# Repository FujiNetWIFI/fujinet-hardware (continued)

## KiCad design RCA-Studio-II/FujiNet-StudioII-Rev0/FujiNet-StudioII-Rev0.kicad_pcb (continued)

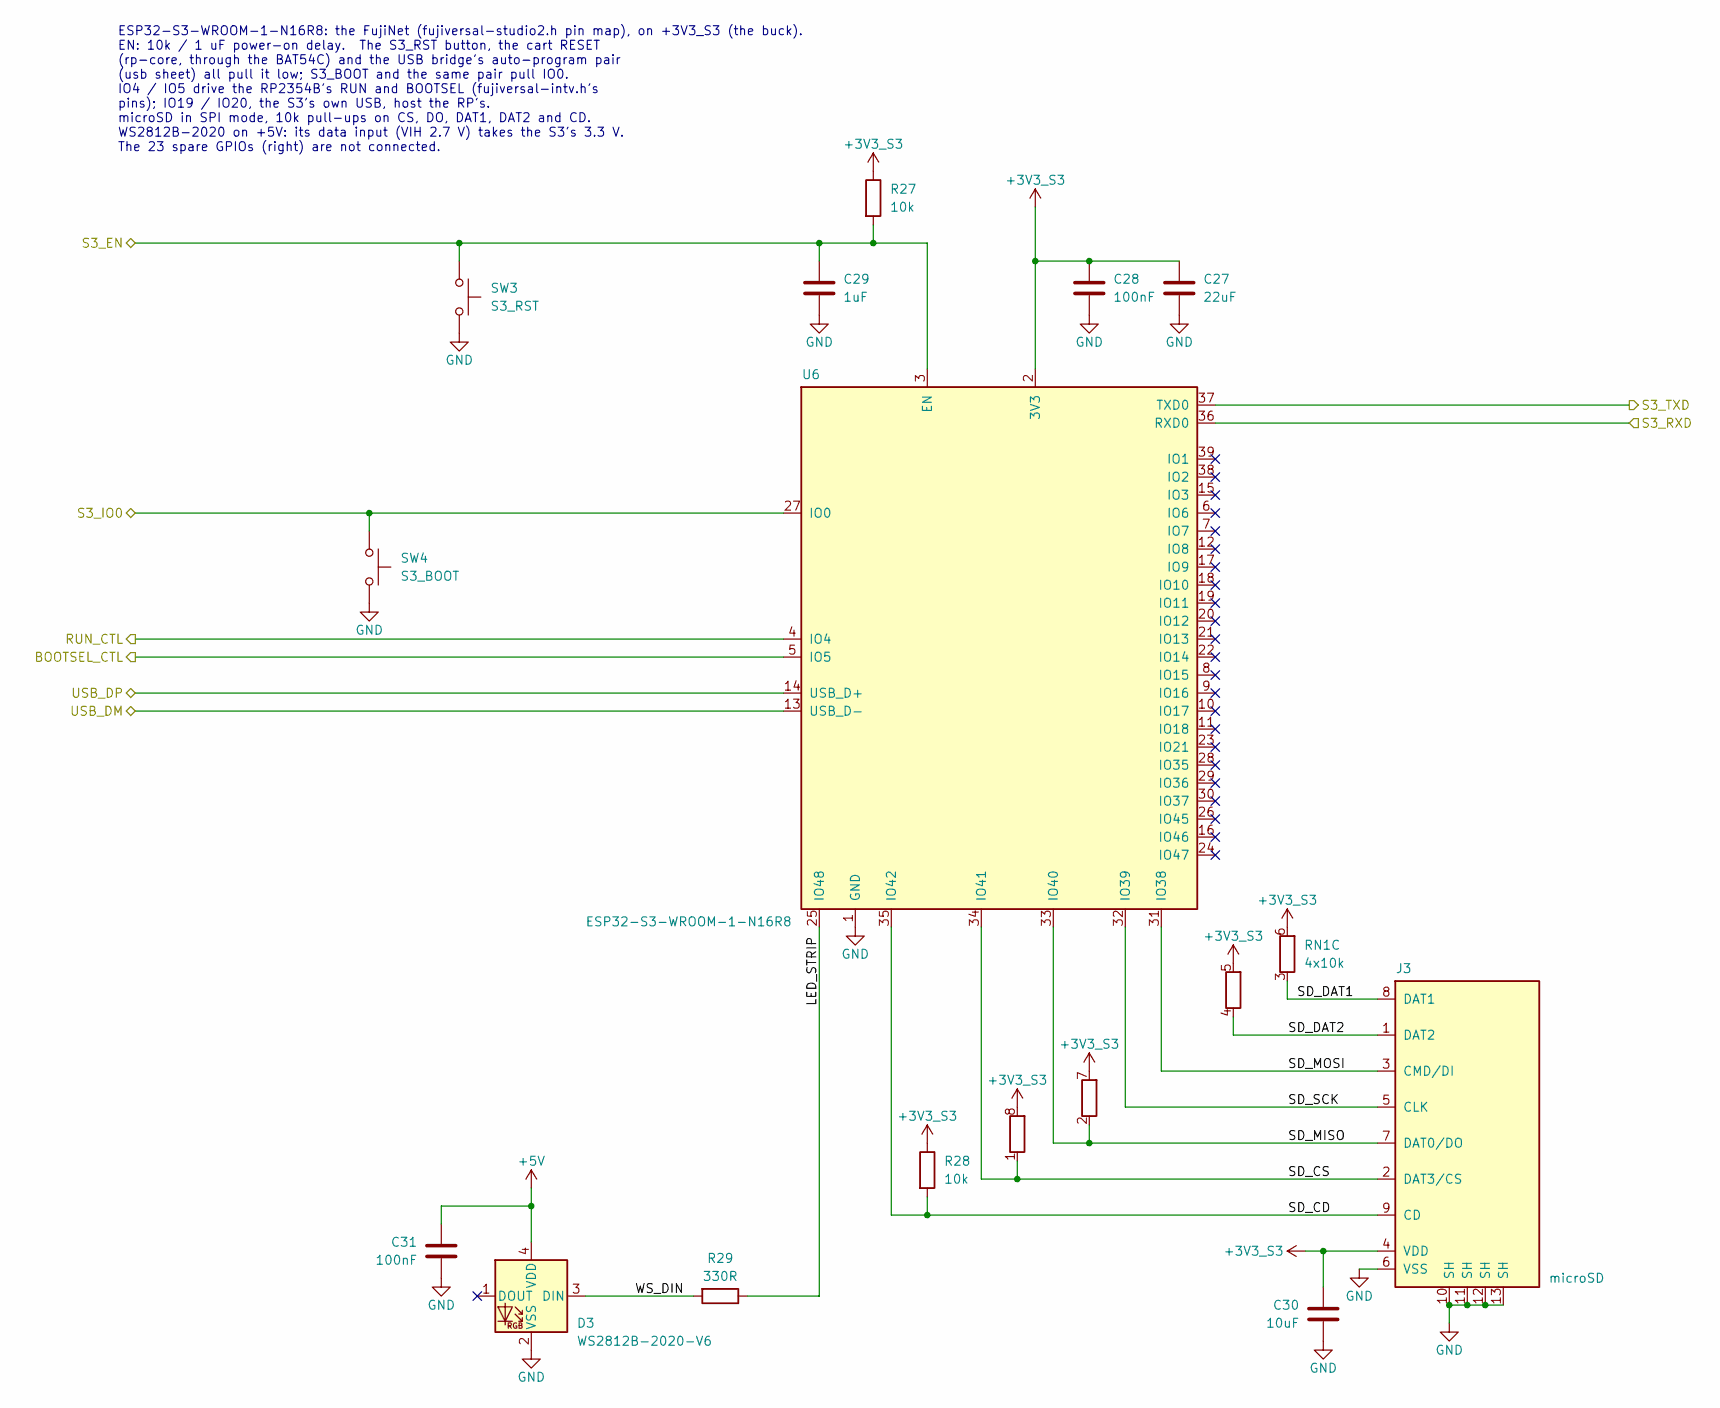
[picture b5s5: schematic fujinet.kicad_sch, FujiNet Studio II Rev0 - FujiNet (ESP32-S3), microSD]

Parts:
C27: 22uF; C_0805_2012Metric; MPN CL21A226MAQNNNE; LCSC C45783
C28, C31: 100nF; C_0603_1608Metric; MPN CC0603KRX7R9BB104; LCSC C14663
C29: 1uF; C_0603_1608Metric; MPN CL10A105KB8NNNC; LCSC C15849
C30: 10uF; C_0603_1608Metric; MPN CL10A106KP8NNNC; LCSC C19702
D3: WS2812B-2020-V6; LED_WS2812B-2020_PLCC4_2.0x2.0mm; MPN WS2812B-2020-V6; LCSC C52917434
J3: microSD; TF-SMD_TF-015; MPN TF-015; LCSC C113206
R27, R28: 10k; R_0603_1608Metric; MPN 0603WAF1002T5E; LCSC C25804
R29: 330R; R_0603_1608Metric; MPN 0603WAF3300T5E; LCSC C23138
RN1: 4x10k; R_Array_Convex_4x0603; MPN 4D03WGJ0103T5E; LCSC C29718
SW3: S3_RST; SW_SPST_TS-1187A; MPN TS-1187A-B-A-B; LCSC C318884
SW4: S3_BOOT; SW_SPST_TS-1187A; MPN TS-1187A-B-A-B; LCSC C318884
U6: ESP32-S3-WROOM-1-N16R8; ESP32-S3-WROOM-1; MPN ESP32-S3-WROOM-1-N16R8; LCSC C2913202

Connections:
+3V3_S3: C27.1, C28.1, C30.1, J3.4 (VDD), R27.1, R28.1, RN1.5 (R4.2), RN1.6 (R3.2), RN1.7 (R2.2), RN1.8 (R1.2), U6.2 (3V3); also elsewhere on the board
+5V: C31.1, D3.4 (VDD); also elsewhere on the board
/BOOTSEL_CTL: U6.5 (IO5); also elsewhere on the board
/RUN_CTL: U6.4 (IO4); also elsewhere on the board
/S3_EN: C29.1, R27.2, SW3.1, U6.3 (EN); also elsewhere on the board
/S3_IO0: SW4.1, U6.27 (IO0); also elsewhere on the board
/S3_RXD: U6.36 (RXD0); also elsewhere on the board
/S3_TXD: U6.37 (TXD0); also elsewhere on the board
/USB_DM: U6.13 (USB_D-); also elsewhere on the board
/USB_DP: U6.14 (USB_D+); also elsewhere on the board
/fujinet/LED_STRIP: R29.1, U6.25 (IO48)
/fujinet/SD_CD: J3.9 (CD), R28.2, U6.35 (IO42)
/fujinet/SD_CS: J3.2 (DAT3/CS), RN1.1 (R1.1), U6.34 (IO41)
/fujinet/SD_DAT1: J3.8 (DAT1), RN1.3 (R3.1)
/fujinet/SD_DAT2: J3.1 (DAT2), RN1.4 (R4.1)
/fujinet/SD_MISO: J3.7 (DAT0/DO), RN1.2 (R2.1), U6.33 (IO40)
/fujinet/SD_MOSI: J3.3 (CMD/DI), U6.31 (IO38)
/fujinet/SD_SCK: J3.5 (CLK), U6.32 (IO39)
/fujinet/WS_DIN: D3.3 (DIN), R29.2
GND: C27.2, C28.2, C29.2, C30.2, C31.2, D3.2 (VSS), J3.6 (VSS), J3.10 (SH), J3.11 (SH), J3.12 (SH), J3.13 (SH), SW3.2, SW4.2, U6.1 (GND), U6.40 (GND), U6.41 (GND); also elsewhere on the board

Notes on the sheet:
ESP32-S3-WROOM-1-N16R8: the FujiNet (fujiversal-studio2.h pin map), on +3V3_S3 (the buck). EN: 10k / 1 uF power-on delay. The S3_RST button, the cart RESET (rp-core, through the BAT54C) and the USB bridge's auto-program pair (usb sheet) all pull it low; S3_BOOT and the same pair pull IO0. IO4 / IO5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

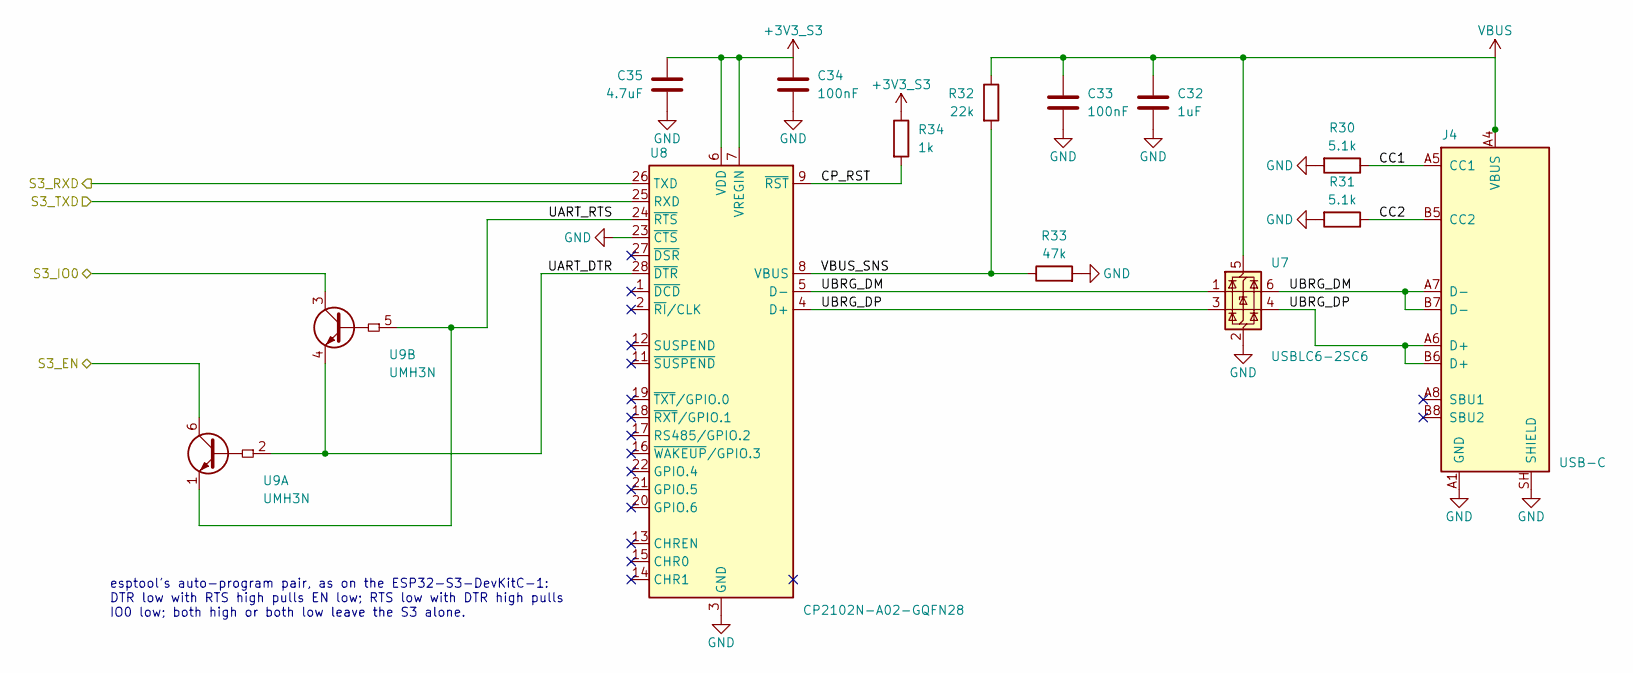
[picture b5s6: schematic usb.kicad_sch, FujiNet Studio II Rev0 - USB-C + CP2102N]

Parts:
C32: 1uF; C_0603_1608Metric; MPN CL10A105KB8NNNC; LCSC C15849
C33, C34: 100nF; C_0603_1608Metric; MPN CC0603KRX7R9BB104; LCSC C14663
C35: 4.7uF; C_0603_1608Metric; MPN CL10A475KO8NNNC; LCSC C19666
J4: USB-C; USB_C_Receptacle_HRO_TYPE-C-31-M-12; MPN TYPE-C-31-M-12; LCSC C165948
R30, R31: 5.1k; R_0603_1608Metric; MPN 0603WAF5101T5E; LCSC C23186
R32: 22k; R_0603_1608Metric; MPN 0603WAF2202T5E; LCSC C31850
R33: 47k; R_0603_1608Metric; MPN 0603WAF4702T5E; LCSC C25819
R34: 1k; R_0603_1608Metric; MPN 0603WAF1001T5E; LCSC C21190
U7: USBLC6-2SC6; SOT-23-6; MPN USBLC6-2SC6; LCSC C7519
U8: CP2102N-A02-GQFN28; QFN-28-1EP_5x5mm_P0.5mm_EP3.35x3.35mm; MPN CP2102N-A02-GQFN28R; LCSC C964632
U9: UMH3N; SOT-363_SC-70-6; MPN UMH3N; LCSC C62892

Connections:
+3V3_S3: C34.1, C35.1, R34.1, U8.6 (VDD), U8.7 (VREGIN); also elsewhere on the board
/S3_EN: U9.6 (C1); also elsewhere on the board
/S3_IO0: U9.3 (C2); also elsewhere on the board
/S3_RXD: U8.26 (TXD); also elsewhere on the board
/S3_TXD: U8.25 (RXD); also elsewhere on the board
/usb/CC1: J4.A5 (CC1), R30.1
/usb/CC2: J4.B5 (CC2), R31.1
/usb/CP_RST: R34.2, U8.9 (~RST)
/usb/UART_DTR: U8.28 (~DTR), U9.2 (B1), U9.4 (E2)
/usb/UART_RTS: U8.24 (~RTS), U9.1 (E1), U9.5 (B2)
/usb/UBRG_DM: J4.A7 (D-), J4.B7 (D-), U7.1 (I/O1), U7.6 (I/O1), U8.5 (D-)
/usb/UBRG_DP: J4.A6 (D+), J4.B6 (D+), U7.3 (I/O2), U7.4 (I/O2), U8.4 (D+)
/usb/VBUS_SNS: R32.2, R33.1, U8.8 (VBUS)
GND: C32.2, C33.2, C34.2, C35.2, J4.A1 (GND), J4.A12 (GND), J4.B1 (GND), J4.B12 (GND), J4.SH (SHIELD), R30.2, R31.2, R33.2, U7.2 (GND), U8.3 (GND), U8.23 (~CTS), U8.29 (GND); also elsewhere on the board
VBUS: C32.1, C33.1, J4.A4 (VBUS), J4.A9 (VBUS), J4.B4 (VBUS), J4.B9 (VBUS), R32.1, U7.5 (VBUS); also elsewhere on the board

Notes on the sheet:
esptool's auto-program pair, as on the ESP32-S3-DevKitC-1: DTR low with RTS high pulls EN low; RTS low with DTR high pulls IO0 low; both high or both low leave the S3 alone.

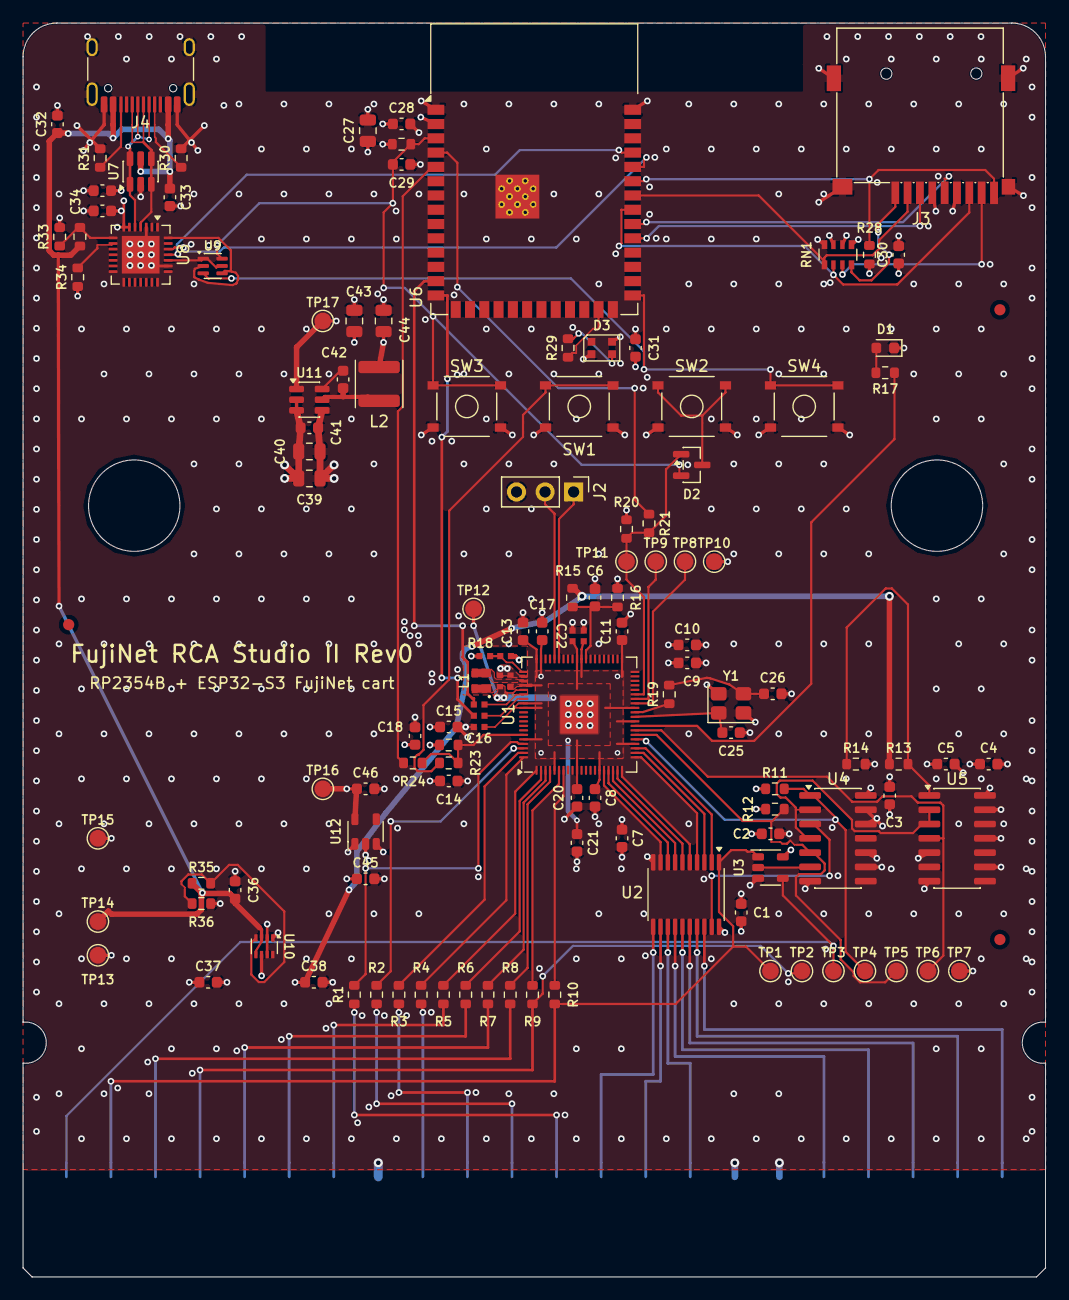
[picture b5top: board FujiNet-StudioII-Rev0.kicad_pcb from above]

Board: 4 copper layers, 90.9 x 111.5 mm, 131 parts (0 on the bottom side), 97 nets.

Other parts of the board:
FID1, FID2, FID3: Fiducial_1mm_Mask2mm
H1, H2: MountingHole_8.128mm_NPTH

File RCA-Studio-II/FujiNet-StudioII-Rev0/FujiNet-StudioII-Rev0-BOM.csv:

Qty,References,Value,Footprint,MPN,Manufacturer,LCSC,Description,Notes
23,C1 C2 C3 C4 C6 C7 C8 C9 C10 C11 C13 C14 C15 C17 C20 C21 C28 C31 C33 C34 C38 C41 C42,100nF,C_0603_1608Metric,CC0603KRX7R9BB104,YAGEO,C14663,capacitor (several uses: see schematic),
4,C5 C18 C30 C37,10uF,C_0603_1608Metric,CL10A106KP8NNNC,Samsung Electro-Mechanics,C19702,capacitor (several uses: see schematic),
3,C12 C16 C22,100nF,RPI_C0402,CL05B104KO5NNNC,Samsung Electro-Mechanics,C1525,capacitor (several uses: see schematic),
2,C19 C23,4.7uF,RPI_C0402_wide,CL05A475MP5NRNC,Samsung Electro-Mechanics,C23733,capacitor (several uses: see schematic),
1,C24,4.7uF,RPI_C0402,CL05A475MP5NRNC,Samsung Electro-Mechanics,C23733,VREG_AVDD filter,
2,C25 C26,15pF,C_0603_1608Metric,CL10C150JB8NNNC,Samsung Electro-Mechanics,C1644,crystal load,
5,C27 C39 C40 C43 C44,22uF,C_0805_2012Metric,CL21A226MAQNNNE,Samsung Electro-Mechanics,C45783,capacitor (several uses: see schematic),
5,C29 C32 C36 C45 C46,1uF,C_0603_1608Metric,CL10A105KB8NNNC,Samsung Electro-Mechanics,C15849,capacitor (several uses: see schematic),
1,C35,4.7uF,C_0603_1608Metric,CL10A475KO8NNNC,Samsung Electro-Mechanics,C19666,CP2102N VDD bulk,
1,D1,red,LED_0603_1608Metric,KT-0603R,Hubei KENTO Elec,C2286,activity LED (GPIO27),
1,D2,BAT54C,SOT-23,"BAT54C,215",Nexperia,C37704,"RESET steering, common cathode",
1,D3,WS2812B-2020-V6,LED_WS2812B-2020_PLCC4_2.0x2.0mm,WS2812B-2020-V6,Worldsemi,C52917434,status LED on +5V (datasheet VDD 3.7-5.3 V; VIH 2.7 V takes 3.3 V data),
1,J1,StudioII_Cart_Edge_22,StudioII_Cart_Edge_22,,,,"RCA Studio II 22-pin cartridge edge, 0.156"" (3.9624 mm) pitch, contacts on one face (B.Cu), FliP multicart geometry",not in BOM
1,J2,DBG UART,PinHeader_1x03_P2.54mm_Vertical,PZ254V-11-03P,XFCN,C2937625,"RP debug UART, 3.3 V: 1 TX (GPIO44), 2 RX (GPIO45), 3 GND; fit for bring-up",DNP
1,J3,microSD,TF-SMD_TF-015,TF-015,SOFNG,C113206,"microSD push-push, SPI mode",
1,J4,USB-C,USB_C_Receptacle_HRO_TYPE-C-31-M-12,TYPE-C-31-M-12,Korean Hroparts Elec,C165948,power + S3 programming / console,
1,L1,3.3uH,RPI_L_AOTA-B201610S3R3,AOTA-B201610S3R3-101-T,Abracon,C42411119,RP2350 core SMPS inductor,
1,L2,6.8uH,L_Sunlord_SWPA4030S,SWPA4030S6R8MT,Sunlord,C62684,buck inductor,
11,R1 R2 R3 R4 R5 R6 R7 R8 R9 R10 R29,330R,R_0603_1608Metric,0603WAF3300T5E,UNI-ROYAL,C23138,resistor (several uses: see schematic),
7,R11 R12 R20 R22 R27 R28 R36,10k,R_0603_1608Metric,0603WAF1002T5E,UNI-ROYAL,C25804,resistor (several uses: see schematic),
2,R13 R32,22k,R_0603_1608Metric,0603WAF2202T5E,UNI-ROYAL,C31850,resistor (several uses: see schematic),
3,R14 R15 R16,100k,R_0603_1608Metric,0603WAF1003T5E,UNI-ROYAL,C25803,resistor (several uses: see schematic),
6,R17 R19 R21 R23 R24 R34,1k,R_0603_1608Metric,0603WAF1001T5E,UNI-ROYAL,C21190,resistor (several uses: see schematic),
1,R18,33R,RPI_R0402,0402WGF330JTCE,UNI-ROYAL,C25105,VREG_AVDD filter,
2,R25 R26,27R,RPI_R0402,0402WGF270JTCE,UNI-ROYAL,C25100,USB series,
2,R30 R31,5.1k,R_0603_1608Metric,0603WAF5101T5E,UNI-ROYAL,C23186,UFP Rd,
1,R33,47k,R_0603_1608Metric,0603WAF4702T5E,UNI-ROYAL,C25819,VBUS sense divider,
1,R35,33k,R_0603_1608Metric,0603WAF3302T5E,UNI-ROYAL,C4216,mux priority threshold (VBUS > 4.3 V),
1,RN1,4x10k,R_Array_Convex_4x0603,4D03WGJ0103T5E,UNI-ROYAL,C29718,SD pull-ups,
1,SW1,BOOTSEL,SW_SPST_TS-1187A,TS-1187A-B-A-B,XKB Connection,C318884,RP2354 BOOTSEL (hold while pressing RESET),
1,SW2,RESET,SW_SPST_TS-1187A,TS-1187A-B-A-B,XKB Connection,C318884,cart RESET: RP RUN + S3 EN via BAT54C,
1,SW3,S3_RST,SW_SPST_TS-1187A,TS-1187A-B-A-B,XKB Connection,C318884,ESP32-S3 EN,
1,SW4,S3_BOOT,SW_SPST_TS-1187A,TS-1187A-B-A-B,XKB Connection,C318884,ESP32-S3 BOOT (IO0),
1,TP1,/MRD,TestPoint_Pad_D1.5mm,,,,scope pad: console /MRD (edge 21),not in BOM
1,TP2,TPA,TestPoint_Pad_D1.5mm,,,,"scope pad: console TPA, gated by /MRD (edge 19)",not in BOM
1,TP3,CART_CS,TestPoint_Pad_D1.5mm,,,,scope pad: CART CS (edge 22),not in BOM
1,TP4,/DRIVE,TestPoint_Pad_D1.5mm,,,,scope pad: /DRIVE (GPIO24),not in BOM
1,TP5,/CLAIM,TestPoint_Pad_D1.5mm,,,,scope pad: NOR input (GPIO25),not in BOM
1,TP6,PWR_OK,TestPoint_Pad_D1.5mm,,,,scope pad: console power sense,not in BOM
2,TP7 TP10,GND,TestPoint_Pad_D1.5mm,,,,test pad (several uses: see schematic),not in BOM
1,TP8,SWCLK,TestPoint_Pad_D1.5mm,,,,test pad,not in BOM
1,TP9,SWDIO,TestPoint_Pad_D1.5mm,,,,test pad,not in BOM
1,TP11,RUN,TestPoint_Pad_D1.5mm,,,,test pad,not in BOM
1,TP12,DVDD,TestPoint_Pad_D1.5mm,,,,bring-up pad: RP core rail,not in BOM
1,TP13,CONS_5V,TestPoint_Pad_D1.5mm,,,,bring-up pad: console 5V (edge 15),not in BOM
1,TP14,VBUS,TestPoint_Pad_D1.5mm,,,,bring-up pad: USB VBUS,not in BOM
1,TP15,+5V,TestPoint_Pad_D1.5mm,,,,bring-up pad: +5V,not in BOM
1,TP16,+3V3,TestPoint_Pad_D1.5mm,,,,bring-up pad: +3V3 (RP),not in BOM
1,TP17,+3V3_S3,TestPoint_Pad_D1.5mm,,,,bring-up pad: +3V3_S3 (S3 side),not in BOM
1,U1,RP2354B,QFN-80-1EP_10x10mm_P0.4mm_EP3.4x3.4mm,RP2354B,Raspberry Pi,C39843328,RP2350B + 2MB flash in package; cart bus server,
1,U2,74HCT541,TSSOP-20_4.4x6.5mm_P0.65mm,SN74HCT541PWR,Texas Instruments,C436096,D0-D7 driver: drives only while /OE1 (/MRD) and /OE2 (/DRIVE) are low,
1,U3,74HCT1G02,SOT-23-5,"74HCT1G02GV,125",Nexperia,C12504,"CART CS = NOR(/MRD, CS_REQ_N), 5 V CMOS out",
1,U4,74HCT32,SOIC-14_3.9x8.7mm_P1.27mm,SN74HCT32DR,Texas Instruments,C6781,/OE2 = /DRIVE | /PWROK; CS_REQ_N = /CLAIM | /PWROK,
1,U5,74HCT14,SOIC-14_3.9x8.7mm_P1.27mm,SN74HCT14DR,Texas Instruments,C6769,PWR_OK from the console 5V sense,
1,U6,ESP32-S3-WROOM-1-N16R8,ESP32-S3-WROOM-1,ESP32-S3-WROOM-1-N16R8,Espressif,C2913202,FujiNet core (fujiversal-studio2),
1,U7,USBLC6-2SC6,SOT-23-6,USBLC6-2SC6,STMicroelectronics,C7519,"USB ESD: D+, D-, VBUS",
1,U8,CP2102N-A02-GQFN28,QFN-28-1EP_5x5mm_P0.5mm_EP3.35x3.35mm,CP2102N-A02-GQFN28R,Silicon Labs,C964632,USB-UART for S3 flashing/console (self-powered),
1,U9,UMH3N,SOT-363_SC-70-6,UMH3N,Jiangsu Changjing (JSCJ),C62892,esptool auto-program (DevKitC-1 style),
1,U10,TPS2116,SOT-583-8,TPS2116DRLR,Texas Instruments,C3235557,"power mux: VBUS first, console 5V second",
1,U11,AP63203WU,TSOT-23-6,AP63203WU-7,Diodes Incorporated,C780769,3.3V 2A buck for the S3 side,
1,U12,AP2112K-3.3,SOT-23-5,AP2112K-3.3TRG1,Diodes Incorporated,C51118,"RP2354B 3.3V LDO (IOVDD, VREG_VIN, VREG_AVDD), 600mA, fast start",
1,Y1,12MHz,Crystal_SMD_3225-4Pin_3.2x2.5mm,ABM8-272-T3,Abracon,C20625731,RP2350 12 MHz crystal,

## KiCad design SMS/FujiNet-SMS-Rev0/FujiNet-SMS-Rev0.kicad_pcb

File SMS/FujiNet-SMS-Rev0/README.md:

# FujiNet-SMS Rev0

All-in-one **Sega Master System / SMS2 FujiNet cartridge**: one board in the
50-pin cartridge slot carrying both halves of the FujiNet stack.

- **RP2354B** (RP2350B die + 2 MB flash, QFN-80, all 48 GPIO used) runs the
  `fujisms` cart firmware from `fujinet-firmware/pico/sms`. It sits on the
  5 V cart bus through its 5 V-tolerant pads (GPIO0-31), serves the mailbox
  arena and the loader itself, and drives SRAM A13-A19 from the live mapper's
  page table (GPIO41-47, the pads that are *not* 5 V tolerant).
- **2x AS6C4008-55** (512K x 8, TSOP-I-32) = 1 MB on the 5 V rail: console
  A0-A12 and D0-D7 direct, the RP's bank lines A13-A18, SRAM A19 picks the chip.
- **74HCT14 / 27 / 27 / 10 / 00** on 5 V: SRAM /OE, /WE and chip select from
  the console's address and strobes and four RP mode bits, plus PWR_OK.
- **ESP32-S3-WROOM-1-N16R8** runs the **`fujiversal-sms`** build of
  fujinet-firmware and is the USB *host* of the RP on IO19/IO20; it re-flashes
  the RP over PICOBOOT.
- **USB-C** (power + CP2102N UART with UMH3N auto-program), **microSD**,
  **WS2812C-2020** status LED, RESET / BOOTSEL / S3 EN / S3 BOOT buttons: the
  NES Rev0 FujiNet half.

**Status (2026-10-08): Rev0 v2 designed, routed and packaged for JLCPCB and PCBWay, not built.**
Nothing has run on a console.

- Schematic: ERC 0 at every severity; `tools/check_nets.py` 442/442 against
  the firmware headers; `tools/check_glue.py` 8192/8192 input combinations
  against the firmware's own glue functions; every sheet mirrors the board
  (below).
- Board: 6 layers, 100 x 93 mm, routed; KiCad DRC at every severity: 0
  violations, 0 unconnected, 0 schematic-parity issues; `check_vias.py` clean.
- Fab: `exports/jlcpcb/` and `exports/pcbway/`, checked by `tools/audit/check_fab.py`
  and `check_gerbers.py`; build-day stock in `docs/sourcing.md`.
- Shell: an OpenSCAD clamshell on the original cartridge's base (`case/`).
- Audit: kicad-happy + manufacturer datasheets, `docs/design-review-rev0.md`.

### What v2 changed (2026-10-08)

The first routed layout (branch `sms-rev0-layout`, 8213d1d) placed parts the
usual way and drew the schematic separately. v2 designs them together:

- **The board was laid out fresh from the edge** (`docs/floorplan-study.md`).
  The SMS edge is the JEDEC 32-pin memory pinout unrolled, so SRAM0 stands
  upright in the classic ROM spot and takes A0-A12, D0-D7 and GND straight from
  the fingers with no crossing. That fan-in is generated and locked before
  routing. The RP2354B sits straight north of it, SRAM1 west, the glue east
  over the strobes, the FujiNet half along the top edge.
- **The schematic was redrawn to mirror the board.** Every sheet is the board
  turned so the fingers face left, with its parts where they sit and every
  connection a wire. Details under *Schematic*.
- **RP2350-E9:** 4.7k pull-downs on GAME, LOAD, RAM_WE, MBOX and SA19, so a pad
  left as an input cannot latch at ~2.2 V and enable /OE, /WE or both SRAMs.
- **Bring-up pads** on every rail (CONS_5V, +5V, +3V3, +3V3_RP, DVDD) and on
  /CE, SRAM /OE, SRAM /WE and PWR_OK, with scope GNDs.
- **Stock swaps:** TS-1187A buttons (the TL3342 had 5 in stock) and the
  WS2812C-2020 (the WS2812B-2020 had 5).
- **Geographic references:** numbered by where each part sits, top to bottom
  and left to right (`tools/annotate.py`, `tools/refs.lock`). J1 stays the edge.
  Every reference below is v2's; the first layout's differ.
- **PCBWay package** next to JLCPCB's; JLC's gerbers carry the order-number box.

The three circuit fixes from the first audit stay:
- a 4.7k VBUS pull-down (the SS34's leakage lifted the P-FET's gate);
- the /WAIT gate pull-up 4.7k (GPIO34's reset pull-down);
- 10 uF on the console's 5 V.

## Edge connector

50 pins, **2.54 mm pitch**, pin 2k-1 directly behind pin 2k.

- The **even pins (2-50) are on the component side**, which faces the label and the front of the console.
- **Pins 1/2 are at the right** seen from the front with the fingers down.

Sources:
- SMS Power's slot diagram;
- little-scale's 32K cart build;
- the component-side silkscreen of an original 171-5519 board (1200 dpi scan, "50 ... 2");
- raphnet's SMS4MBIT drawing;
- the barbeque and reidrac KiCad footprints.

All of them agree. `tools/audit/edge_orientation.py` records them and checks the footprint, and `check_nets.py` asserts the face split.

The pin list is Patrik's corrected physical order (The Hardware Book). SMS Power's table mislabels 31/33/35/37.

| | |
|---|---|
| Fingers | 1.75 x 8.75 mm, copper 0.75-9.5 mm from the edge. Original: 1.65-1.76 wide, ~1.2-10.1 mm; the open designs fall in the same range. |
| Tab | 65.8 mm wide (the original board is 66.0), 15 mm deep, 1 mm chamfers. The body widens to 100 mm above it. |
| Board | 1.6 mm (VERIFY: open designs use 1.6; no original measured). Hard gold, 30-45 degree bevel. |

| Pin | Signal | Net | Pin | Signal | Net |
|---|---|---|---|---|---|
| 1 | +5V | CONS_5V | 2 | /WR | WR_N |
| 3 | /MREQ | MREQ_N | 4 | /RD | RD_N |
| 5 | /M8-B | nc | 6 | A14 | A14 |
| 7 | A13 | A13 | 8 | A8 | A8 |
| 9 | A9 | A9 | 10 | A11 | A11 |
| 11 | /M0-7 | nc | 12 | A10 | A10 |
| 13 | /CE | CE_N | 14 | D7 | D7 |
| 15 | D6 | D6 | 16 | D5 | D5 |
| 17 | D4 | D4 | 18 | D3 | D3 |
| 19 | GND | GND | 20 | GND | GND |
| 21 | GND | GND | 22 | D2 | D2 |
| 23 | D1 | D1 | 24 | D0 | D0 |
| 25 | A0 | A0 | 26 | A1 | A1 |
| 27 | A2 | A2 | 28 | A3 | A3 |
| 29 | A4 | A4 | 30 | A5 | A5 |
| 31 | A6 | A6 | 32 | A7 | A7 |
| 33 | A12 | A12 | 34 | /CONT | CONT_N (TP16) |
| 35 | +5V | CONS_5V | 36 | A15 | A15 |
| 37 | /M1 | M1_N | 38 | /IORQ | IORQ_N |
| 39 | /RFSH | nc | 40 | /HALT | nc |
| 41 | /WAIT | WAIT_N | 42 | /INT | nc |
| 43 | KILLGA | nc | 44 | /BUSREQ | BUSREQ_N (TP15) |
| 45 | /BUSACK | nc | 46 | /RESET | RESET_N |
| 47 | CLK | CLK | 48 | /KBSEL | nc |
| 49 | /MC-F | nc | 50 | /NMI | nc |

/M8-B, /M0-7, /MC-F, /RFSH, /HALT, /INT, /NMI, /KBSEL, KILLGA and /BUSACK are
open. /CONT and /BUSREQ (inputs to the console) end on test pads TP16 / TP15
only, and nothing is fitted. /CONT is a general input the I/O chip reports on
the second controller port, not a boot or cart-detect line (the BIOS finds the
`TMR SEGA` header). Stock carts leave both open. /WAIT is driven only by the
2N7002 (Q1); the console holds its pull-up.

## RP2354B pin map

Exactly `sms_cart.h`; `tools/check_nets.py` reads the header and checks the
netlist against it.

| GPIO | Net | Goes to |
|---|---|---|
| 0-15 | A0-A15 | edge and SRAM A0-A12; A12-A15 also the glue |
| 16-23 | RP_D0-7 | RN2 / RN3 (4 x 100R) to D0-D7: edge, both SRAM DQ |
| 24-31 | RD_N WR_N MREQ_N CE_N IORQ_N RESET_N M1_N CLK | edge 4, 2, 3, 13, 38, 46, 37, 47; RD/WR/CE also the glue |
| 32 | PWR_OK | 74HCT14 output (console +5V sense), also the glue |
| 33 | RP_LED | R24 1k, red LED D7 |
| 34 | WAIT_GATE | Q1 2N7002 gate (R25 4.7k pull-up to +3V3_RP); drain = edge 41 /WAIT |
| 35, 38, 39, 40 | MBOX, GAME, RAM_WE, LOAD | glue inputs; 4.7k RP2350-E9 pull-downs |
| 36, 37 | DBG_TX, DBG_RX | J4 pins 1, 2 (pin 3 GND), DNP |
| 41-46 | SA13-SA18 | both SRAMs A13-A18 |
| 47 | SA19 | SRAM0 U10 /CE (4.7k E9 pull-down); U12C -> SA19_N -> SRAM1 U7 /CE |

GPIO40-47 are not 5 V tolerant. `check_nets.py` asserts their nets carry
nothing but input pins: glue and SRAM inputs on the 5 V rail, whose HCT
(VIH 2.0 V) and AS6C4008 (VIH 2.4 V at 4.5-5.5 V) thresholds the RP's
3.3 V outputs meet, with 0.22 V to spare at worst. QFN-80 pin numbers are
checked against `MCU_RaspberryPi:RP2354B` by `gen_sch.py`. The core (crystal,
SMPS, USB, RUN/BOOTSEL, SWD) is the NES Rev0 circuit.

**RP2350-E9** (the A2 stepping; fixed in A3/A4, but the stepping a buyer gets
is not guaranteed): a Bank 0 pad set as an input, with its output off and its
voltage between VIL and VIH, sources ~120 uA and sits near 2.2 V. A pull of
8.2k or less to GND overcomes it (datasheet p.1366-1367). R18-R22 (4.7k) hold
SA19, MBOX, GAME, RAM_WE and LOAD at 0.56 V or less against it
(`tools/audit/margins.py`), and cost 0.7 mA each while the RP drives them high.

## Glue

All 74HCT on +5V; the equations are `sms_glue_oe()` / `sms_glue_we()` in
`sms_cart.h`. RD, WR, CE = the console's strobes asserted; GAME, MBOX, RAM_WE,
LOAD active high from the RP; PWR_OK = console +5V present.

```
HIGH16 = A15 & A14     SLOT2 = A15 & !A14     WIN8 = SLOT2 & !A13     ARENA = SLOT2 & A13 & A12
/OE asserted = PWR_OK & GAME & RD & CE & !HIGH16 & !(MBOX & ARENA)
/WE asserted = PWR_OK & CE & (LOAD & RD & WIN8  |  RAM_WE & WR & SLOT2 & !(MBOX & ARENA))
U10 /CE = SA19          U7 /CE = !SA19
```

Five packages, all 19 gates used (the cart-bus sheet draws them as a wired
network by logic depth, under the strobes that feed them):

| Net | Gate | Function |
|---|---|---|
| PWR_OK_N, PWR_OK | U12A, U12B ('14) | Schmitt of 0.82 x CONS_5V, twice |
| SA19_N, CE, A15_N, MBA | U12C-F ('14) | inversions (MBA = !MBA_N) |
| CEP_N | U11A ('00) | !(CE & PWR_OK) |
| MBA_N | U8A ('10) | !(MBOX & A13 & A12) |
| WIN8 | U13B ('27) | NOR(A15_N, A14, A13) |
| SLOT2_NM | U13C ('27) | NOR(A15_N, A14, MBA) = SLOT2 & !(MBOX & ARENA) |
| RD_CEP | U13A ('27) | NOR(RD_N, CEP_N) |
| LOADWIN_N | U11B ('00) | !(LOAD & WIN8) |
| RAMWIN_N | U8B ('10) | !(RAM_WE & SLOT2_NM) |
| SLOT2_NM_N, OE_ADDR | U11C, U11D ('00) | OE_ADDR = !A15 \| SLOT2_NM = !HIGH16 & !(MBOX & ARENA) |
| WE_LOAD, WE_RAM | U9A, U9B ('27) | NOR(RD_N, CEP_N, LOADWIN_N), NOR(WR_N, CEP_N, RAMWIN_N) |
| SRAM_WE_N | U9C ('27) | NOR(WE_LOAD, WE_RAM) |
| SRAM_OE_N | U8C ('10) | NAND(RD_CEP, GAME, OE_ADDR) |

`tools/check_glue.py` builds this network from the netlist, taking the gate
tables from the pin numbers rather than from `design.py`. It evaluates the
network for all 2^13 inputs and compares the result with `sms_cart.h`
compiled on the host and with the equations above. It also checks the
structure:
- /RD and /WR reach /WE through **two** gates (the write ends two NOR3 delays after the strobe does);
- /RD reaches /OE through two gates;
- /CE reaches /OE and /WE through four ('14, '00, '27, '27/'10).

Timing (Z80 at 3.58 MHz, T = 279 ns; `tools/audit/timing_margins.py`; PROVISIONAL until measured):
- **/CE is on the critical /OE path.** On SMS1/SMS2 the slot's /CE is /MREQ
  gated by the I/O chip's slot enable, so it falls together with /RD, not long
  before it. An M1 fetch samples data about 1.5 T after /RD falls. Against that
  are the four gates from /CE (121 ns worst case) plus the AS6C4008's 55 ns:
  +108 ns of margin, assuming the console decodes /CE in 40 ns (no published
  figure). Memory reads have +233 ns.
- **The bank lines are not static.** SA13-SA19, including SA19 as chip select,
  follow the live mapper: core1 puts the 1K page's bank on every address change.
  That leaves 359 ns for an M1 fetch (71 cycles at 200 MHz) and 483 ns for
  memory reads.
- **RAM_WE write.** /WE rises at most 52 ns after /WR (two '27s). The Z80 holds
  data at least 69.7 ns (+17.7 ns) and the address at least 89.7 ns (+37.7 ns).
- **LOAD copy.** The SRAM is written during a console *read* of $8000-$9FFF,
  with the RP driving D0-D7. The RP must keep driving until /WE rises, two '27
  delays after /RD does; the firmware's 150 ns drive gives +98 ns.

With the TI alternates (CD74HCT27M96 / CD74HCT10M, `timing_margins.py --ti`)
every margin stays positive: +105 ns on the M1 fetch, +11.7 ns write-data hold.

Firmware contract the glue needs:
- Set **LOAD** only while the console copies with plain data reads, never while
  it executes from $8000-$9FFF. In an opcode fetch the refresh address replaces
  A0-A15 as /RD rises.
- Keep **GAME = 0 while LOAD = 1**: together they assert /OE and /WE at once.

## Power

- **Sources:** the NES Rev0 arrangement. Console +5V (edge 1/35, `CONS_5V`)
  goes through **Q2, an AO3401A P-FET** whose gate is VBUS. Without USB the
  gate is held at 0 V by R3 (4.7k) and the FET is fully on. With USB, only its
  body diode remains, so USB never back-feeds the console. USB VBUS comes in
  through **D1, an SS34**. Both meet on **+5V**. R3 is there because the
  SS34's reverse leakage (up to 20 mA hot) flows into VBUS. With only the 69k
  sense divider, 100 uA already turned the FET off (`tools/audit/spice_checks.py`).
- **+5V:** both SRAMs, the five 74HCT packages, the WS2812C, the AP63203 buck
  (U5) and the AP2112K LDO (U6). **+3V3** (buck): ESP32-S3, microSD, CP2102N.
  **+3V3_RP** (LDO, tracks the 5 V rail): every RP2354B supply pin, so its
  pads are powered before the console's bus levels reach them.
- **Console budget:** the cart draws about 460 mA peak (the S3 transmitting,
  through the buck) and 185 mA on average from the console's 7805. There is
  10 uF + 100 nF at the fingers. Use a **1 A adaptor**: SMS2 adaptors were
  0.5 A in some regions. Measure the console rail under WiFi load at bring-up.
- **USB with the console on** (for flashing) turns the FET off: +5V =
  VBUS - VF(SS34) = 4.3-4.9 V, which can be under the 74HCTs' 4.5 V minimum.
  Use it for flashing, not for play.
- **PWR_OK** is sensed on `CONS_5V`, before the FET: R26 / R27, 22k / 100k
  (0.82 x), into a 74HCT14 Schmitt (TTL thresholds, VT+ 1.2-1.9 V), inverted
  twice, to GPIO32 and the glue. It is a console-present sense (rises at
  2.3-2.6 V), not a brown-out detector. With USB in and the console off, /OE
  and /WE stay high, so nothing but the RP can drive the dead bus; its firmware
  keys off GPIO32 and CLK.

## Flashing

As on NES Rev0:
- **S3:** over USB-C (CP2102N, esptool auto-program).
- **RP:** by the S3 over PICOBOOT: IO4 -> 1k -> RUN and IO5 -> 1k -> QSPI_SS, driven low to assert.
- **Manual BOOTSEL:** hold SW4 (BOOTSEL) while pressing SW2 (RESET).
- **SWD:** TP3 SWCLK / TP4 SWDIO, with TP5 GND and TP6 RUN.
- **RP debug UART:** J4 (DNP, 3-pin 2.54 mm header).
- **S3:** SW1 is its EN (reset), SW3 its BOOT (IO0).

## Board

100 x 78 mm body on a 65.8 x 15 mm tab (93 mm overall), **1.6 mm, 6 layers**
(the NES Rev0 stack):

| Layer | Use |
|---|---|
| F.Cu | every part, the even fingers, signals + GND pour |
| In1 | GND plane |
| In2, In3 | signals |
| In4 | +3V3 plane in the north band; a +5V island over the south and up the east edge (console 5V, SRAMs, glue, LDO input, buck input); a +3V3_RP island under the RP2354B ring; a DVDD island under its core |
| B.Cu | the odd fingers, signals + GND pour (no parts) |

Floorplan (`tools/placement.py`, variant P3, chosen by trial routing in
`docs/floorplan-study.md`; top view, fingers down):
- **SRAM0 (U10)** upright in the ROM spot over the fingers, its pin 17-32 end
  down: A0-A12, D0-D7 and GND reach it from the fingers without a crossing. The
  fan-in (`gen_pcb.sram0_fanin()`) is drawn and locked before routing.
- **RP2354B (U4)** straight north of SRAM0, its A/D side facing it, with the
  NES Rev0 decoupling ring, crystal, core regulator and USB / QSPI corner (same
  package, rotation and circuit). The D0-D7 100R packs RN2 / RN3 sit at its data pins.
- **SRAM1 (U7)** west of SRAM0; **the glue** east, over the strobes that feed it
  (/RD /WR /MREQ /CE and A13/A14), next to the RP's strobe side.
- **North band:** the ESP32-S3 (antenna top-left over its keep-out), the
  microSD and the USB-C / CP2102N / buck corner.
- **West edge:** the four buttons, the LEDs and the debug header, under the
  shell's pinholes and windows; the scope and rail pads beside them.
- **Screw holes:** four M3, with a 3 mm part-free ring each.

Routing (`tools/route_board.sh`):
1. The SRAM0 fan-in, the RP2354B core corner, the crystal and SWD are drawn or
   routed first on the empty board, and locked.
2. Freerouting runs (12 passes, its default greedy strategy; the best of six variants).
3. A grid A* finisher (`tools/finish_route.py`) closes what Freerouting leaves.
4. Clean-up, GND stitching, `check_vias.py`, then the DRC gate.

Netclasses:
- Default: 0.2 mm track / 0.15 mm clearance.
- Power: 0.5 mm.
- USB pairs: 0.25 mm.

The 0.4 mm-pitch RP pins' final links neck down to 0.15 / 0.12 mm (JLCPCB's
6-layer minimum is 0.09).

The routed board:
- 126 nets, all routed: Freerouting plus the finisher for the last 2 links
  (A12 and QSPI_SS);
- 1961 segments and 6071 mm of track (F.Cu 1119, In2 391, In3 353, B.Cu 98
  segments; In4 carries only the power planes);
- 741 vias, 388 of them GND, 269 of those stitching (a 4 mm grid, an edge guard row, and
  return vias beside the USB vias).

Connector alignment (2026-10-13): the USB-C (J2) moved 1.8 mm to HRO's recommended PCB-edge
position (its face had sat 1.35 mm inside the board, where a plug's overmold meets the PCB edge), and
the microSD / USB-C 3D models were re-seated on their footprints; DRC still 0 / 0 / 0 (design review,
"Post-layout change").

## Schematic

Six sheets: the root, `cart-bus` (A1) and `rp-core`, `fujinet`, `usb`,
`power` (A3), one per board region. **Every sheet is the board turned so the
fingers face left** (board south -> page left, north -> right, west -> top,
east -> bottom). Each part is placed where it sits on the board, and every
connection on a sheet is a wire. Signals flow left to right, from the console
to the USB-C.

- **Root:** the board outline at 2:1, turned the same way, with each sheet's
  block at its region and the nine signals between sheets wired.
- **cart-bus:** the edge on the left; A0-A12 / D0-D7 straight across to SRAM0
  in its ROM spot, then SRAM1 and the RP's GPIO unit; the RN elements inline
  on D0-D7; the glue as a gate network under the strobes; /WAIT, the LED and
  the E9 pull-downs where they sit.
- **rp-core:** the RP2354B's core unit with each supply pin's 100 nF at the
  pin (the board's ring), the regulator corner, crystal, SWD and the RUN /
  BOOTSEL / RESET network.
- **fujinet:** the ESP32-S3 (a functional symbol), its EN RC and buttons, the
  WS2812C, and the microSD's SPI lines stepping into the socket with the
  pull-ups between them.
- **usb:** the USB-C (a functional symbol) facing the CP2102N, and the
  esptool auto-program pair. This page has one crossing, and it cannot be
  avoided: RTS and DTR leave the bridge side by side, and each feeds the base
  of one transistor and the emitter of the other.
- **power:** the CONS_5V / VBUS OR on one +5V line, the LDO above it, the buck
  below it.

Symbols are functional: pins grouped by what they connect to, the stock KiCad
pin names and numbers kept (`gen_sch.verify_pin_tables` checks the RP2354B,
ESP32-S3 and USB-C symbols against the stock ones).

`gen_sch.py` gates the drawing:
- connectivity and overlap lint for every sheet;
- every net a single wired piece per sheet;
- a crossing budget per sheet: cart-bus 75 (the glue network and its feeds),
  usb 1, the rest 0;
- the **mirror check** (`tools/sch_place.py`): on each sheet the major parts
  (ICs, connectors, transistors, switches, the crystal, the LEDs) are in their
  board order across and down the page, Kendall tau >= 0.85 per axis (every
  sheet is at 1.00 / 1.00);
- netlist parity with `design.py`, and the net names equal `tools/nets.lock`,
  the names the board carries.

## Shell

`case/FujiNet-SMS-Shell.scad` (generated anchors in `case/board-anchors.scad`;
dimensions and sources in `case/case-spec.md`):
- **Outside:** 109.1 x 100.9 x 16.9 mm. It keeps the original cartridge's base
  (109.1 x 16.9, the board's component face 8.3 mm inside the label face, the
  contact edge 5.4 mm up inside an open connector mouth) and is 31.6 mm taller.
- **Front (label) half:** label recess, RESET with a printed plunger,
  BOOTSEL / S3 EN / S3 BOOT pin-holes, LED windows, the USB-C and microSD
  openings in the top wall.
- **Rear half:** a flat back plate.
- **Fasteners:** 4x M3x12 from the back.

The SCAD asserts the base width, the cavity, the part clearance (6.3 mm over the tallest part),
the mouth width and the RESET plunger: its cap stands proud by more than the TS-1187A's travel,
and its flange clears the switch body. `-D 'part="interference"'` renders both halves
intersected with the placed plunger and must come out empty (it does: "Current top level
object is empty").

The base dimensions marked VERIFY in `case-spec.md` come from a replica shell,
not a measured cartridge. Check them on SMS1, SMS2 and a Genesis + Power Base
Converter before printing more than one.

## Ordering

`tools/export.py` writes both packages; `tools/audit/check_fab.py` checks them
against the board (designators, CPL positions and rotations, drills, the gerber
gate). Step-by-step instructions are in the packages:

- **JLCPCB:** `exports/jlcpcb/ORDER-JLCPCB.md`, with the gerber zip (its
  silkscreen carries the order-number box), `BOM-JLCPCB.csv`,
  `CPL-JLCPCB.csv` (rotations and origins measured per part against EasyEDA,
  `tools/audit/jlc/`) and `consigned.csv`.
- **PCBWay:** `exports/pcbway/ORDER-PCBWay.md`, with the gerber zip,
  `BOM-PCBWay.csv` (MPN and manufacturer per line), `Centroid-PCBWay.csv`
  (KiCad's own rotations) and `Assembly-top.pdf`.

Both need: 6 layers, 1.6 mm, ENIG, **gold fingers with a 30-45 degree bevel**,
filled vias for the vias in the RP2354B's exposed pad, and assembly on the top
side. JLCPCB needs **Standard PCBA** (the RP2354B is 0.4 mm pitch).

Three lines are not in JLCPCB's stock (`docs/sourcing.md`): the AS6C4008-55TIN
SRAMs and the Nexperia 74HCT27D / 74HCT10D. Consign them, use JLC's Global
Sourcing, or order PCBWay turnkey.

**Before ordering either (VERIFY):**
1. **The tab.** Print `docs/tab-overlay-1to1.pdf` at 100 %, check its 50 mm
   ruler, and lay a real SMS cartridge board on the fingers: even fingers on
   the label side, pins 1/2 at the right, finger span and tab width.
2. **The thickness:** measure a real cartridge board (1.6 mm assumed).
3. **The TSOPs' pin 1** in the assembler's placement preview: EasyEDA has no
   footprint for the AS6C4008-55TIN, so its CPL rotation is the TSOP-I
   convention and is marked low confidence. The board's silkscreen marks pin 1
   boldly.

## Regenerating

KiCad 10.0.6, Python 3 (+ numpy), a C compiler (for `check_glue.py`); for the
board also Java and Freerouting 2.4.1
(`~/.local/share/freerouting/freerouting-2.4.1.jar`).

```sh
export FUJINET_FIRMWARE=~/Workspace/fn-sms FUJINET_SMS_BOARD=~/Workspace/fn-sms-board
tools/build_all.sh               # schematic, ERC, firmware checks, BOM / PDF, fab packages
LAYOUT=1 tools/build_all.sh      # + board: placement, routing, DRC with schematic parity, CPL / gerbers / renders
tools/audit/run_sch_audit.sh     # kicad-happy schematic audit + deep review gate
tools/audit/run_pcb_audit.sh     # kicad-happy PCB / cross / EMC / thermal / gerber audit + fab release gate
python3 tools/audit/check_fab.py # the two fab packages against the board
python3 tools/audit/sourcing.py  # build-day stock -> docs/sourcing.md (needs the network)
python3 tools/tab_overlay.py     # docs/tab-overlay-1to1.pdf
openscad -D 'part="front"' -o front.stl case/FujiNet-SMS-Shell.scad   # also "rear", "plunger"
```

Firmware heads checked: `~/Workspace/fn-sms` (`add-sms`, 10f055b87) and
`~/Workspace/fn-sms-board` (302d4950d). `check_*.py` read:
- `$FUJINET_FIRMWARE/pico/sms`. `build_all.sh` defaults to `~/Workspace/fn-sms`,
  the `add-sms` branch, when it exists.
- `$FUJINET_SMS_BOARD/include/pinmap/fujiversal-sms.h` (default
  `~/Workspace/fn-sms-board`). `fujiversal-sms.h` does not define
  `PIN_RP2040_RUN/BOOTSEL` yet, so `check_nets.py` falls back to
  `fujiversal-intv.h` (IO4/IO5) and says so.

Edit `tools/design.py` (circuit), `tools/sch_layout.py` (drawing) and
`tools/placement.py` (board), never the KiCad files. Freerouting is not deterministic, so
`LAYOUT=1` reproduces the method (12 passes, greedy, then the finisher), not the same copper;
the committed board is the reviewed one.

- **Parts are addressed by key.** Every part has a design.py key (`U_RP`,
  `C_IOV5`, ...). The drawing, the placement and the audits use keys;
  references come from `tools/refs.lock` (geographic, `tools/annotate.py`).
- **Hierarchy.** The sheets join through hierarchical labels, wired on the
  root. KiCad names nets `/USB_DP` (root), `/cart-bus/A0` (one sheet) or `GND`
  (power symbols); `tools/nets.lock` freezes them.
- **Checks.** `sch_draw.py` lints connectivity, overlaps and crossings as each
  sheet is drawn; `sch_place.py` holds each sheet to the board;
  `gen_sch.check_hierarchy()` holds the labels and sheet pins to design.py;
  `gen_sch.netlist_parity()` holds KiCad's netlist to it.
- **Placement preview.** `tools/plot_placement.py` draws the placement with the
  ratsnest and prints its length and crossings.

## Parts and sourcing

`docs/sourcing.md` has every line's stock at JLCPCB and LCSC on 2026-10-08,
the quantities for 2 and 5 boards and a parts cost (about USD 29 per board).

- **Not at JLCPCB / LCSC:** AS6C4008-55TIN (C5569980), 74HCT27D,653 (C5984),
  74HCT10D,653 (C547236). All three are at DigiKey / Mouser.
  - TI's **CD74HCT27M96 (C2878706)** and **CD74HCT10M (C2863188)** are
    pin-identical alternates in single-digit stock. Every timing margin stays
    positive with them (`timing_margins.py --ti`).
  - Plain HC parts are not substitutes: the inputs need TTL thresholds.
  - The rest of the glue (SN74HCT14DR C6769, SN74HCT00DR C6764) is stocked.
- **Buttons:** TS-1187A-B-A-B (C318884, JLC basic), as on FujiNet-7800 Rev0.
- **Status LED:** WS2812C-2020-V1 (C2976072): the WS2812B-2020's package, land
  and pins, 5 mA per channel.
- The '27 and '10 use the stock `74LS27` / `74LS10` symbols and the '14 the
  `74HC14` symbol, with the HCT part as the value and its datasheet linked.
- D0-D7 series resistors are two 4 x 100R arrays (`4D03WGJ0101T5E`, C25506).
- Activity LED is red (`KT-0603R`, C2286): GPIO33 drives it from 3.3 V.
- `2N7002` C8545; header `PZ254V-11-03P` C2937625 (DNP).
- Footprints are copies of the NES Rev0 project's (KiCad library geometry, the
  AOTA inductor from Raspberry Pi's RP2350 minimal design, MIT:
  `tools/RPI-MINIMAL-LICENSE.txt`), plus the generated edge and header and the
  7800's TS-1187A. 3D models are in `3d/` (see `3d/README.md`).

## Bring-up checklist (not verifiable in CAD)

1. **Edge before ordering:** the tab overlay above, and the board thickness.
2. **Shell:** the VERIFY list in `case/case-spec.md` on each console model.
3. **Rails before the console:** on USB alone, check +5V (TP11), +3V3 (TP2),
   +3V3_RP (TP7) and DVDD (TP1, ~1.1 V); CONS_5V (TP14) stays at 0 V.
4. **Power-on:** /WAIT must be held by Q1 from the first console cycle until
   the firmware drives GPIO34 low. GAME / MBOX / RAM_WE / LOAD / SA19 sit on
   their 4.7k pull-downs until the firmware drives them.
5. **PWR_OK** (TP12) with USB in and the console off: SRAM /OE (TP9) and /WE
   (TP10) must stay high.
6. **Console 5 V headroom** under WiFi bursts on SMS1 and SMS2 (TP14; the
   7805 feeds the SRAMs, glue, buck and LDO through Q2).
7. **Timing:** scope /CE (TP8) -> SRAM /OE (TP9) on an M1 fetch from SRAM, and
   console D0-D7 against /WE (TP10) on a RAM_WE write; TP13 is the scope GND
   beside them. Then re-tune the PROVISIONAL timings in `sms_cart.c`.
8. **LOAD copy:** verify a loaded image byte for byte.
9. **RP input levels** at /RD, /WR, /CE, CLK against VIH 2.0 V (the FT pads at
   IOVDD 3.3 V).

## Firmware follow-ups (fujinet-firmware; not changed here)

- `fujiversal-sms.h` has no `PIN_RP2040_RUN` / `PIN_RP2040_BOOTSEL`, and
  there is no `pico_usb_reset` path: the S3 cannot yet force BOOTSEL on a
  running RP through IO4 / IO5, though the board wires both.
- IO42 (microSD card detect) and the RP's debug UART (GPIO36/37, J4) are
  wired but unused.
- WiFi TX power is not capped; a cap would ease the console's 5 V budget.

## Provenance and license

**CERN-OHL-W-2.0.** The RP2354B core, the ESP32-S3 / microSD / USB-UART /
power circuits and the generators are from `NES/FujiNet-NES-Rev0` in this
repository (itself from Astrocade Rev0, INTV Rev0 and the PiNTY CARD,
CERN-OHL-W-2.0); the key addressing, CPL method and shell structure from
`ATARI-2600/Fujiversal-Atari2600-Rev1`; the PCBWay package, manufacturer data
and fab checks from `ATARI-7800/FujiNet-7800-Rev0`. Edge pinout: the corrected
SMS / SMS2 slot list (Patrik's sequential order); edge geometry and
orientation: the sources above. Glue equations: `fujinet-firmware` `pico/sms`
`sms_cart.h`. Symbols and footprints: official KiCad libraries (CC-BY-SA 4.0
with exception).

## Files

| Path | Contents |
|---|---|
| `FujiNet-SMS-Rev0.kicad_pro/.kicad_sch` | KiCad 10 project: the root plus `cart-bus`, `rp-core`, `fujinet`, `usb`, `power` |
| `FujiNet-SMS-Rev0.kicad_pcb/.kicad_dru` | the 6-layer board and its custom rules |
| `FujiNet-SMS.kicad_sym`, `FujiNet-SMS.pretty/`, `3d/` | project symbol and footprint libraries, 3D models |
| `FujiNet-SMS-Rev0-BOM.csv` | grouped BOM (DNP flagged) |
| `exports/jlcpcb/`, `exports/pcbway/` | the two fab packages and their order instructions |
| `docs/` | schematic PDF, layout SVGs, board renders, tab overlay, `design-review-rev0.md`, `floorplan-study.md`, `sourcing.md` |
| `case/` | the shell (OpenSCAD), its board anchors and dimension dossier |
| `datasheets/manifest.json` | the datasheets the audit used (PDFs fetched, not committed) |
| `tools/` | generators, checks and the routing pipeline (see *Regenerating*); `tools/audit/` the audit, fab and sourcing scripts and the JLC rotation table |

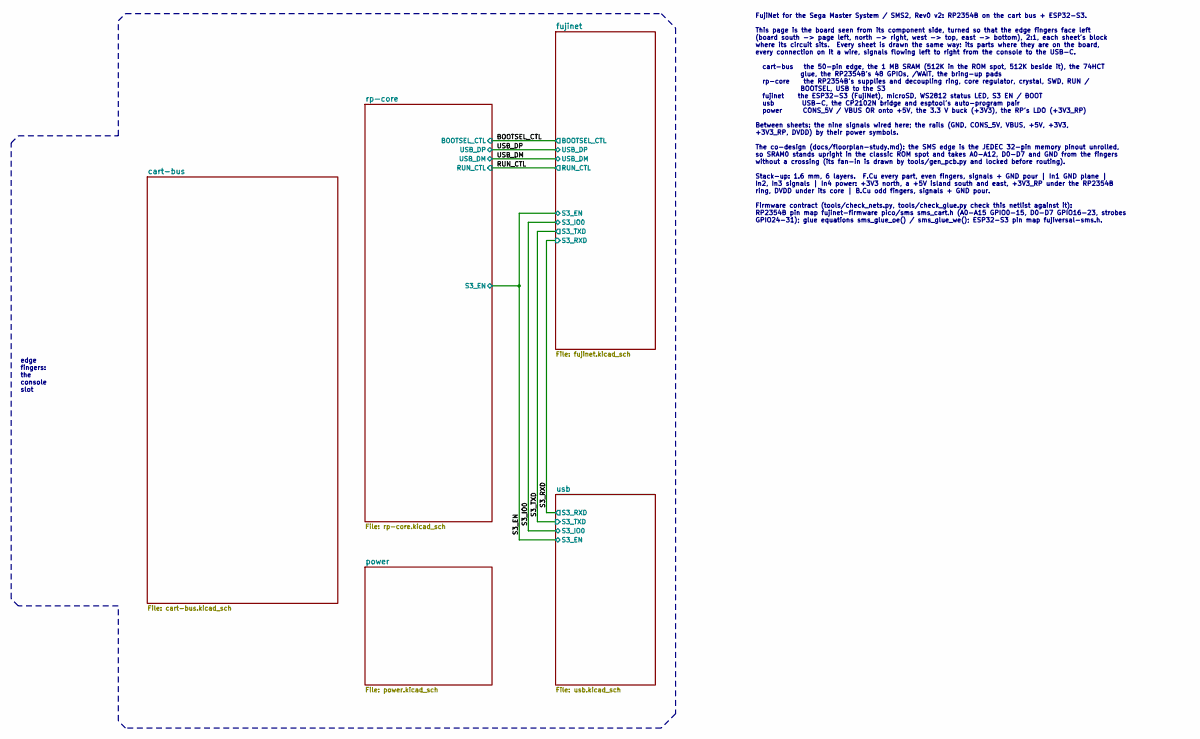
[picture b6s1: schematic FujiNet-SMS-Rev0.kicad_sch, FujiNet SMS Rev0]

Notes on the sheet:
edge fingers: the console slot
FujiNet for the Sega Master System / SMS2, Rev0 v2: RP2354B on the cart bus + ESP32-S3. This page is the board seen from its component side, turned so that the edge fingers face left (board south -> page left, north -> right, west -> top, east -> bottom), 2:1, each sheet's block where its circuit s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
